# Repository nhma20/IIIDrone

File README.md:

# IIIDrone
Hardware and software specifications for the Infrastructure Inspection and Interaction Drone

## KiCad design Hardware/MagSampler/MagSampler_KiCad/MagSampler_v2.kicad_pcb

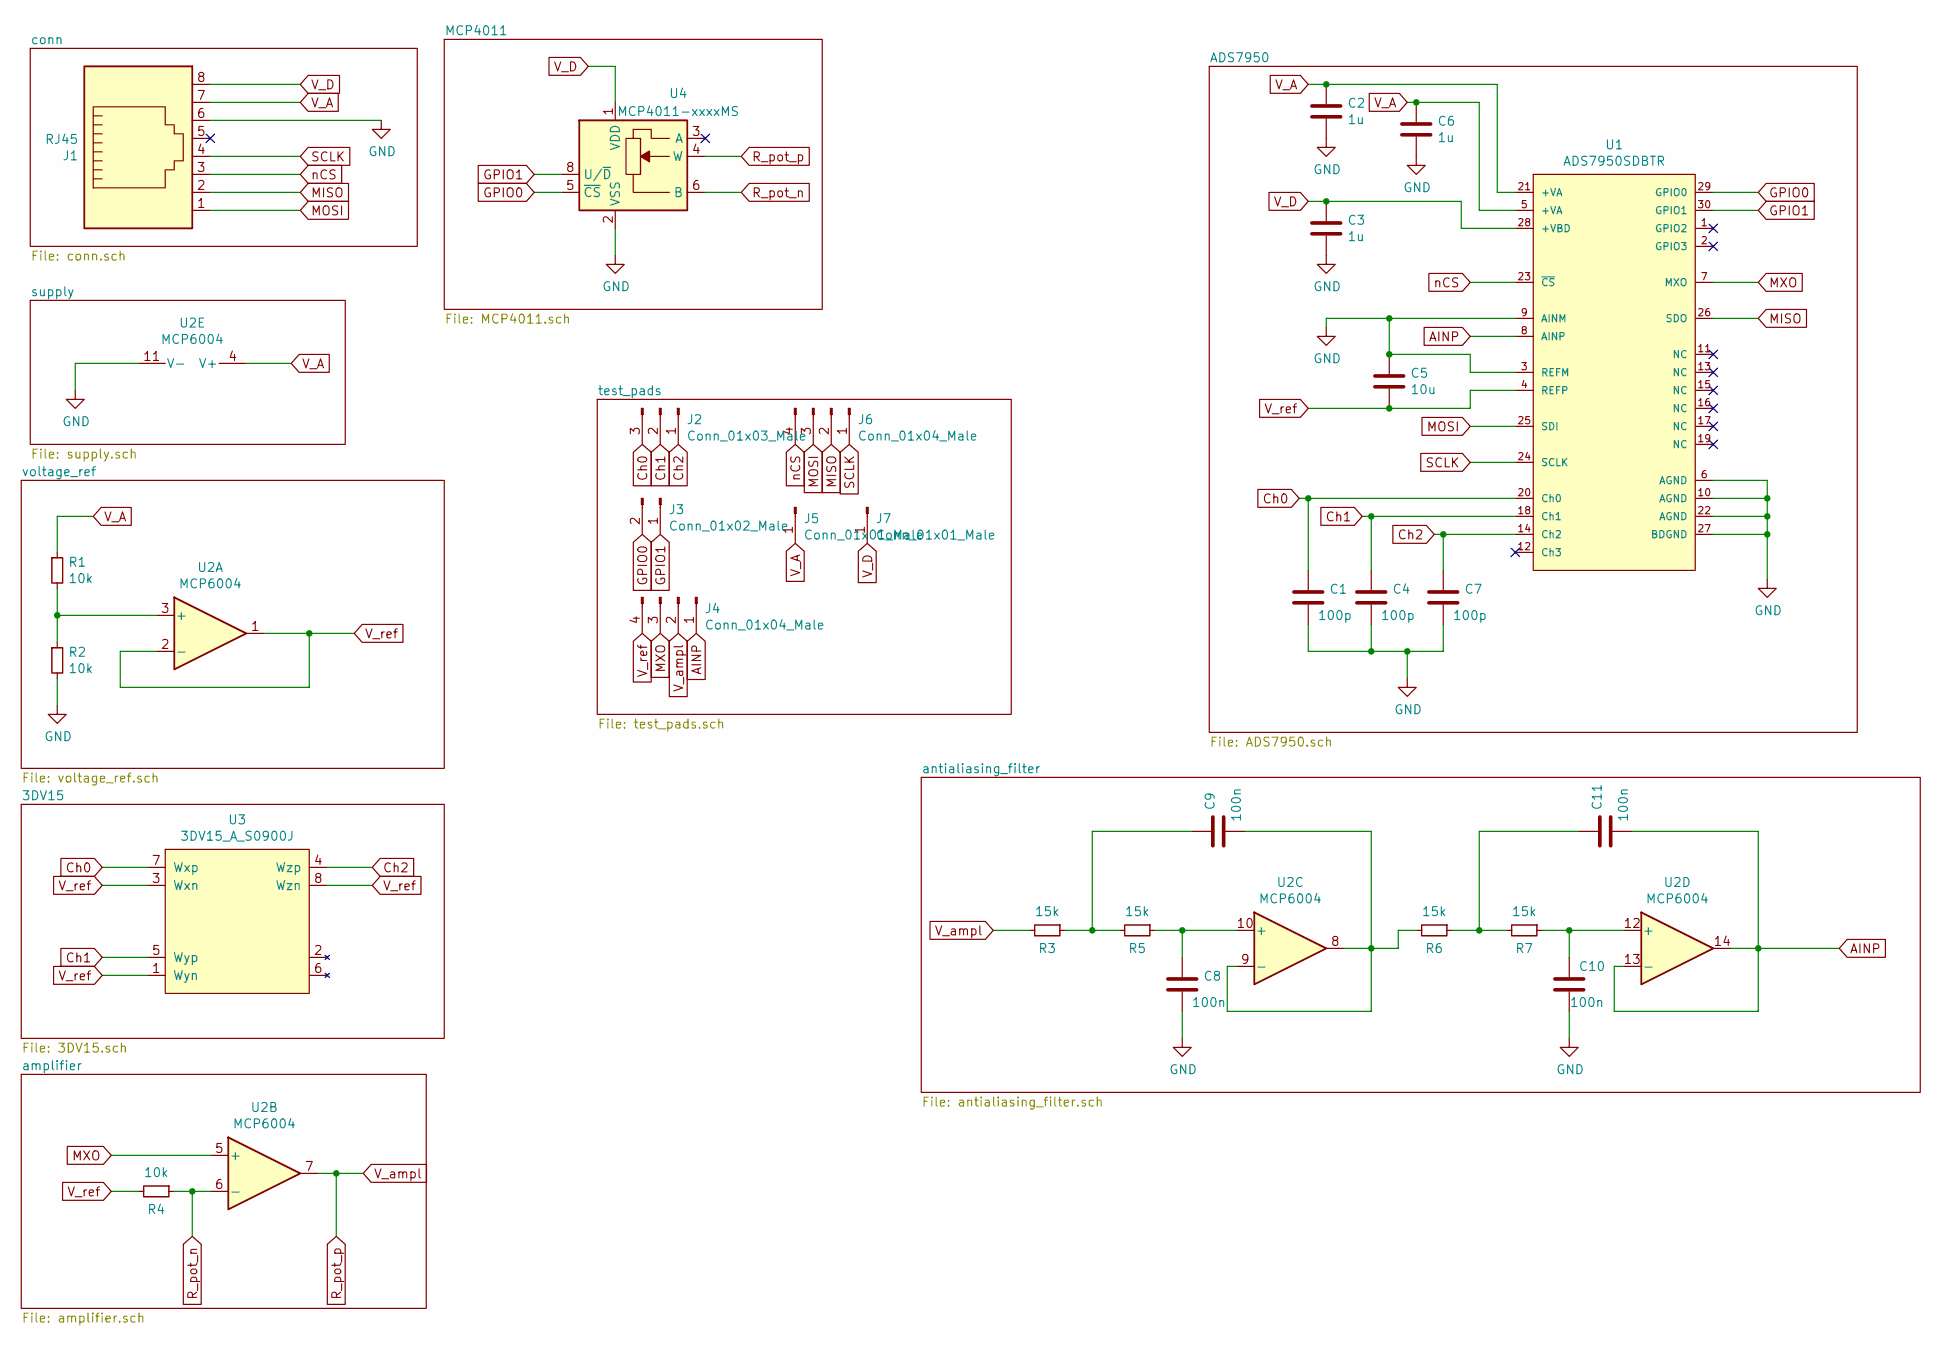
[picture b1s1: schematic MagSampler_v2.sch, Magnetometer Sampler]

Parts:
C1, C4, C7: 100p; C_0805_2012Metric
C2, C3, C6: 1u; C_0805_2012Metric
C5: 10u; C_0805_2012Metric
C8, C9, C10, C11: 100n; C_0805_2012Metric
J1: RJ45; RJ45_Ninigi_GE
J2: Conn_01x03_Male; PinHeader_1x03_P2.54mm_Vertical
J3: Conn_01x02_Male; PinHeader_1x02_P2.54mm_Vertical
J4, J6: Conn_01x04_Male; PinHeader_1x04_P2.54mm_Vertical
J5, J7: Conn_01x01_Male; PinHeader_1x01_P2.54mm_Vertical
R1, R2, R4: 10k; R_0805_2012Metric
R3, R5, R6, R7: 15k; R_0805_2012Metric
U1: ADS7950SDBTR; TSSOP-30_4.4x7.8mm_P0.5mm; mouser part number 595-ADS7950SDBTR; digikey description IC ADC 12BIT SER 1M 30TSSOP
U2: MCP6004; TSSOP-14_4.4x5mm_P0.65mm
U3: 3DV15_A_S0900J
U4: MCP4011-xxxxMS; MSOP-8_3x3mm_P0.65mm

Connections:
AINP: C11.2, J4.1, U1.8 (AINP), U2.13 (-), U2.14
Ch0: C1.1, J2.3, U1.20 (Ch0), U3.7 (Wxp)
Ch1: C4.1, J2.2, U1.18 (Ch1), U3.5 (Wyp)
Ch2: C7.1, J2.1, U1.14 (Ch2), U3.4 (Wzp)
GND: C1.2, C2.2, C3.2, C4.2, C5.1, C6.2, C7.2, C8.2, C10.2, J1.6, R2.2, U1.3 (REFM), U1.6 (AGND), U1.9 (AINM), U1.10 (AGND), U1.22 (AGND), U1.27 (BDGND), U2.11 (V-), U4.2 (VSS)
GPIO0: J3.2, U1.29 (GPIO0), U4.5 (~CS)
GPIO1: J3.1, U1.30 (GPIO1), U4.8 (U/~D)
MISO: J1.2, J6.2, U1.26 (SDO)
MOSI: J1.1, J6.3, U1.25 (SDI)
MXO: J4.3, U1.7 (MXO), U2.5 (+)
unnamed: C8.1, R5.1, U2.10 (+)
unnamed: C9.1, R3.1, R5.2
unnamed: C9.2, R6.2, U2.8, U2.9 (-)
unnamed: C10.1, R7.1, U2.12 (+)
unnamed: C11.1, R6.1, R7.2
unnamed: R1.2, R2.1, U2.3 (+)
R_pot_n: R4.1, U2.6 (-), U4.6 (B)
R_pot_p: J4.2, R3.2, U2.7, U4.4 (W)
SCLK: J1.4, J6.1, U1.24 (SCLK)
V_A: C2.1, C6.1, J1.7, J5.1, R1.1, U1.5 (+VA), U1.21 (+VA), U2.4 (V+)
V_D: C3.1, J1.8, J7.1, U1.28 (+VBD), U4.1 (VDD)
V_ref: C5.2, J4.4, R4.2, U1.4 (REFP), U2.1, U2.2 (-), U3.1 (Wyn), U3.3 (Wxn), U3.8 (Wzn)
nCS: J1.3, J6.4, U1.23 (~CS~)

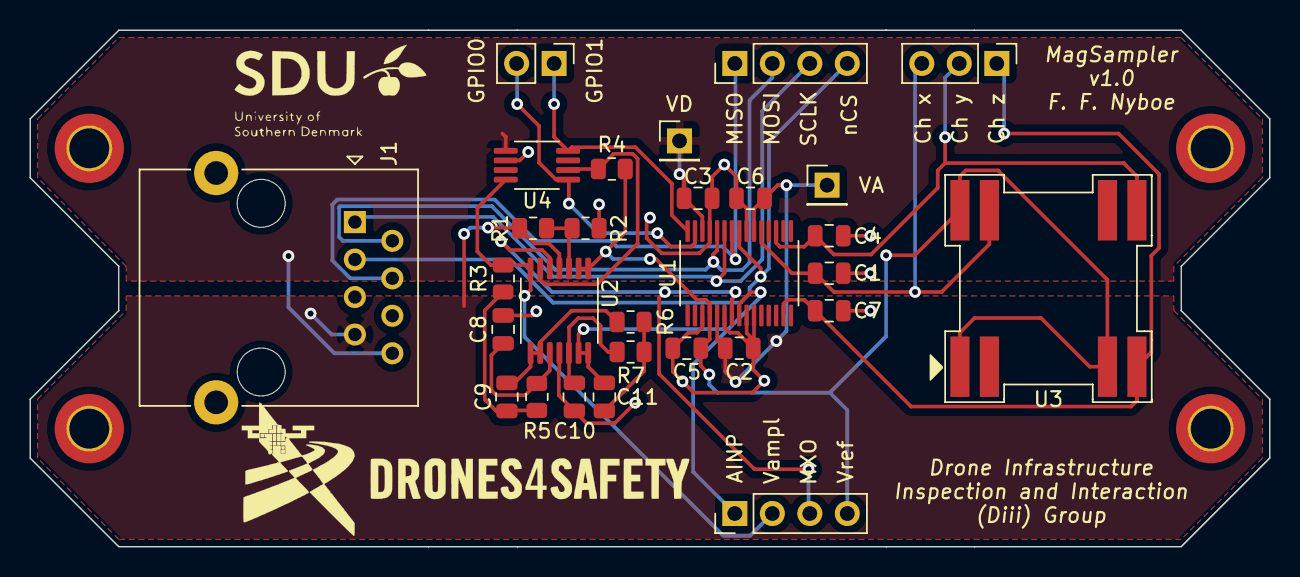
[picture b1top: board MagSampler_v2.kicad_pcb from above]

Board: 2 copper layers, 84.0 x 35.0 mm, 29 parts (0 on the bottom side), 23 nets.

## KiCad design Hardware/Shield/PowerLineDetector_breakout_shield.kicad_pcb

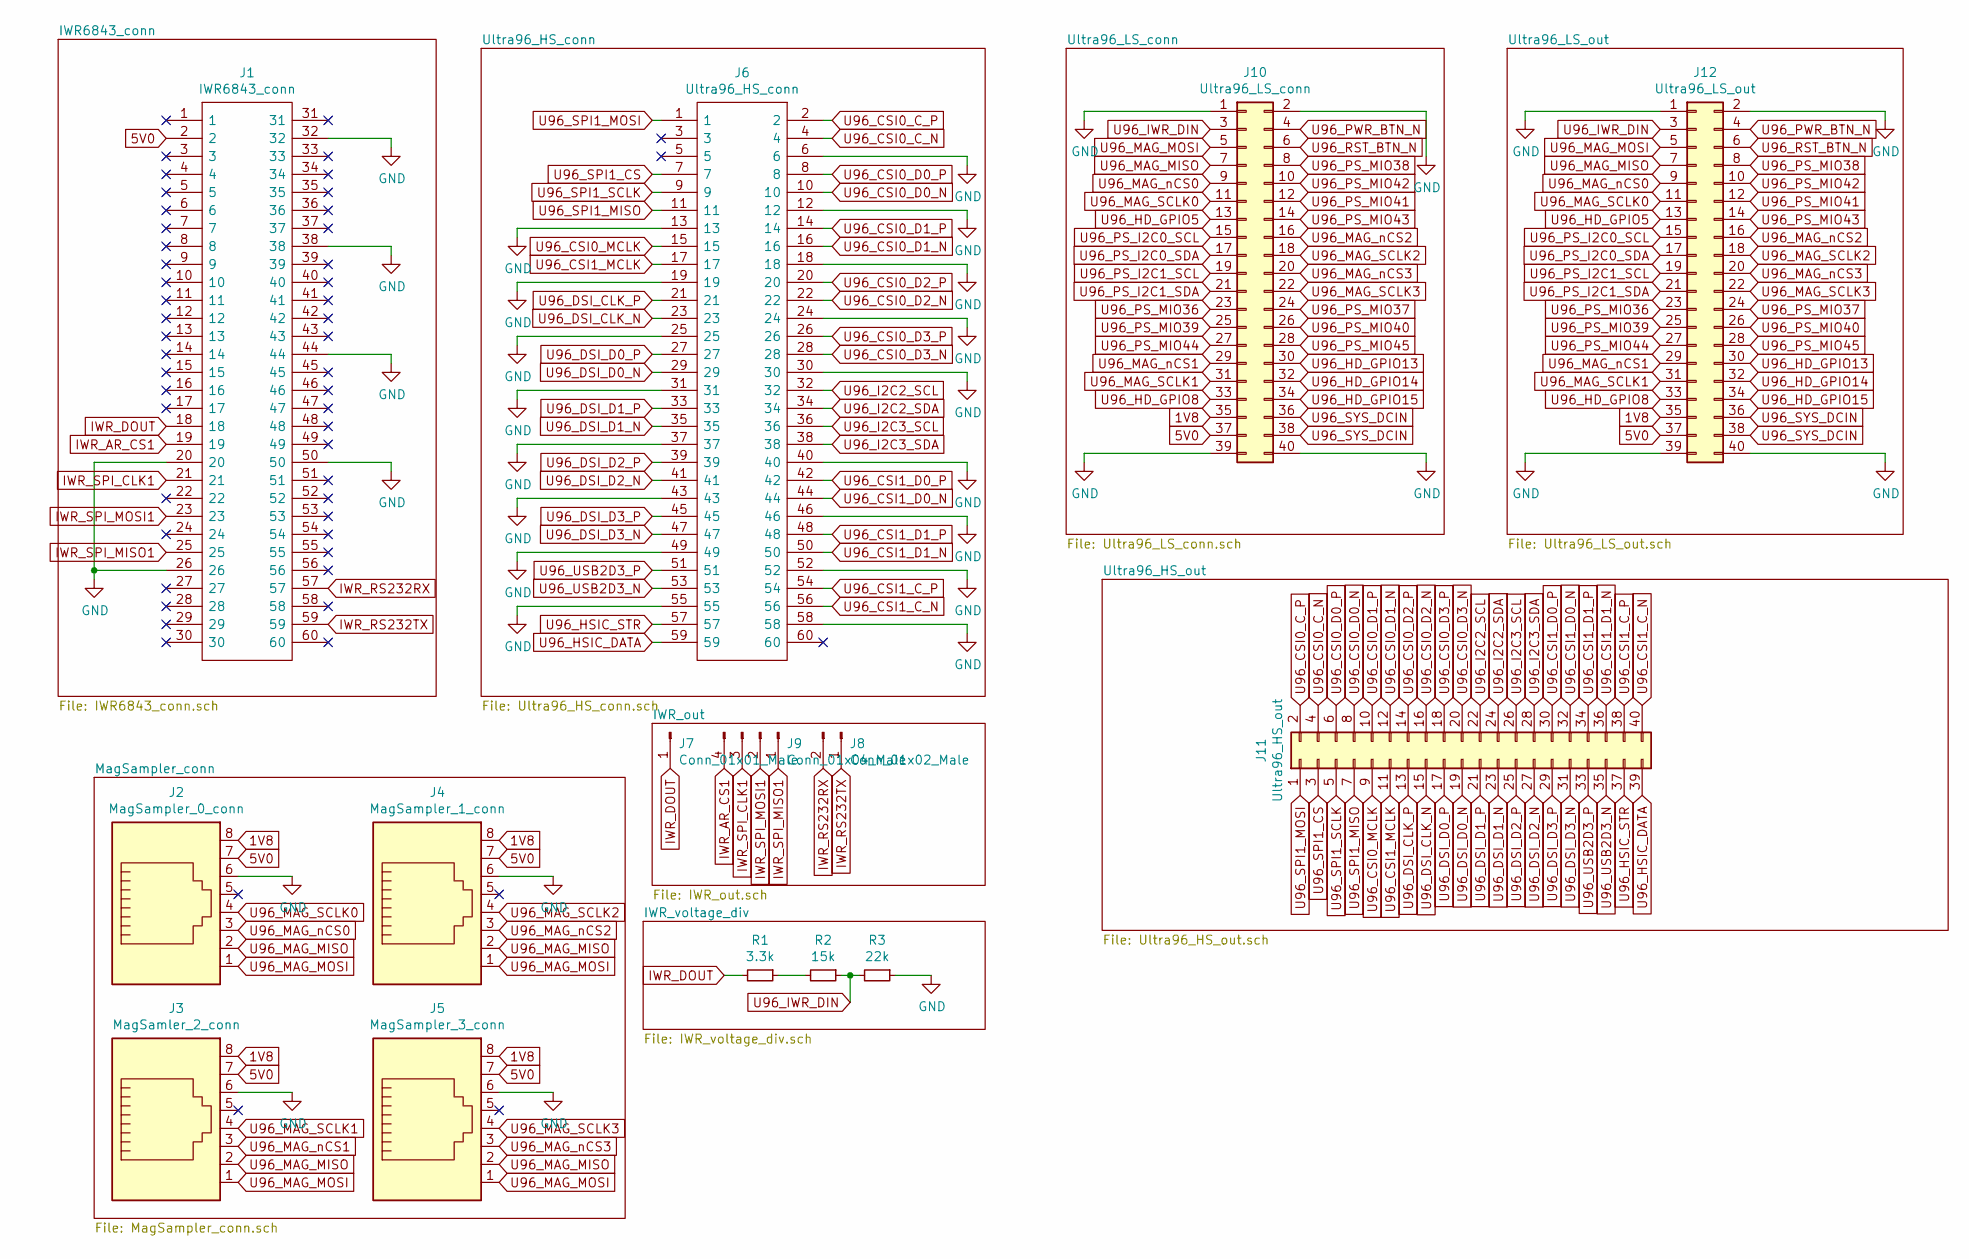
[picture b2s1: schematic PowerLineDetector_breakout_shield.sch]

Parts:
J1: IWR6843_conn; QTH-030-XX-Y-D-A-K-TR; Mouser Part Number 200-QTH03001LDAKTR
J2: MagSampler_0_conn; RJ45_Ninigi_GE
J3: MagSamler_2_conn; RJ45_Ninigi_GE
J4: MagSampler_1_conn; RJ45_Ninigi_GE
J5: MagSampler_3_conn; RJ45_Ninigi_GE
J6: Ultra96_HS_conn; 61083061402LF; Mouser Part Number 649-61083-061402LF
J7: Conn_01x01_Male; PinHeader_1x01_P2.54mm_Vertical
J8: Conn_01x02_Male; PinHeader_1x02_P2.54mm_Vertical
J9: Conn_01x04_Male; PinHeader_1x04_P2.54mm_Vertical
J10: Ultra96_LS_conn; PinSocket_2x20_P2.00mm_Vertical
J11: Ultra96_HS_out; PinHeader_2x20_P2.00mm_Vertical
J12: Ultra96_LS_out; PinHeader_2x20_P2.00mm_Vertical
R1: 3.3k; R_0805_2012Metric
R2: 15k; R_0805_2012Metric
R3: 22k; R_0805_2012Metric

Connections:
1V8: J2.8, J3.8, J4.8, J5.8, J10.35, J12.35
5V0: J1.2, J2.7, J3.7, J4.7, J5.7, J10.37, J12.37
GND: J1.20, J1.26, J1.32, J1.38, J1.44, J1.50, J2.6, J3.6, J4.6, J5.6, J6.6, J6.12, J6.13, J6.18, J6.19, J6.24, J6.25, J6.30, J6.31, J6.37, J6.40, J6.43, J6.46, J6.49, J6.52, J6.55, J6.58, J10.1, J10.2, J10.39, J10.40, J12.1, J12.2, J12.39, J12.40, R3.1
IWR_AR_CS1: J1.19, J9.4
IWR_DOUT: J1.18, J7.1, R1.2
IWR_RS232RX: J1.57, J8.2
IWR_RS232TX: J1.59, J8.1
IWR_SPI_CLK1: J1.21, J9.3
IWR_SPI_MISO1: J1.25, J9.1
IWR_SPI_MOSI1: J1.23, J9.2
unnamed: R1.1, R2.2
U96_CSI0_C_N: J6.4, J11.4
U96_CSI0_C_P: J6.2, J11.2
U96_CSI0_D0_N: J6.10, J11.8
U96_CSI0_D0_P: J6.8, J11.6
U96_CSI0_D1_N: J6.16, J11.12
U96_CSI0_D1_P: J6.14, J11.10
U96_CSI0_D2_N: J6.22, J11.16
U96_CSI0_D2_P: J6.20, J11.14
U96_CSI0_D3_N: J6.28, J11.20
U96_CSI0_D3_P: J6.26, J11.18
U96_CSI0_MCLK: J6.15, J11.9
U96_CSI1_C_N: J6.56, J11.40
U96_CSI1_C_P: J6.54, J11.38
U96_CSI1_D0_N: J6.44, J11.32
U96_CSI1_D0_P: J6.42, J11.30
U96_CSI1_D1_N: J6.50, J11.36
U96_CSI1_D1_P: J6.48, J11.34
U96_CSI1_MCLK: J6.17, J11.11
U96_DSI_CLK_N: J6.23, J11.15
U96_DSI_CLK_P: J6.21, J11.13
U96_DSI_D0_N: J6.29, J11.19
U96_DSI_D0_P: J6.27, J11.17
U96_DSI_D1_N: J6.35, J11.23
U96_DSI_D1_P: J6.33, J11.21
U96_DSI_D2_N: J6.41, J11.27
U96_DSI_D2_P: J6.39, J11.25
U96_DSI_D3_N: J6.47, J11.31
U96_DSI_D3_P: J6.45, J11.29
U96_HD_GPIO5: J10.13, J12.13
U96_HD_GPIO8: J10.33, J12.33
U96_HD_GPIO13: J10.30, J12.30
U96_HD_GPIO14: J10.32, J12.32
U96_HD_GPIO15: J10.34, J12.34
U96_HSIC_DATA: J6.59, J11.39
U96_HSIC_STR: J6.57, J11.37
U96_I2C2_SCL: J6.32, J11.22
U96_I2C2_SDA: J6.34, J11.24
U96_I2C3_SCL: J6.36, J11.26
U96_I2C3_SDA: J6.38, J11.28
U96_IWR_DIN: J10.3, J12.3, R2.1, R3.2
U96_MAG_MISO: J2.2, J3.2, J4.2, J5.2, J10.7, J12.7
U96_MAG_MOSI: J2.1, J3.1, J4.1, J5.1, J10.5, J12.5
U96_MAG_SCLK0: J2.4, J10.11, J12.11
U96_MAG_SCLK1: J3.4, J10.31, J12.31
U96_MAG_SCLK2: J4.4, J10.18, J12.18
U96_MAG_SCLK3: J5.4, J10.22, J12.22
U96_MAG_nCS0: J2.3, J10.9, J12.9
U96_MAG_nCS1: J3.3, J10.29, J12.29
U96_MAG_nCS2: J4.3, J10.16, J12.16
U96_MAG_nCS3: J5.3, J10.20, J12.20
U96_PS_I2C0_SCL: J10.15, J12.15
U96_PS_I2C0_SDA: J10.17, J12.17
U96_PS_I2C1_SCL: J10.19, J12.19
U96_PS_I2C1_SDA: J10.21, J12.21
U96_PS_MIO36: J10.23, J12.23
U96_PS_MIO37: J10.24, J12.24
U96_PS_MIO38: J10.8, J12.8
U96_PS_MIO39: J10.25, J12.25
U96_PS_MIO40: J10.26, J12.26
U96_PS_MIO41: J10.12, J12.12
U96_PS_MIO42: J10.10, J12.10
U96_PS_MIO43: J10.14, J12.14
U96_PS_MIO44: J10.27, J12.27
U96_PS_MIO45: J10.28, J12.28
U96_PWR_BTN_N: J10.4, J12.4
U96_RST_BTN_N: J10.6, J12.6
U96_SPI1_CS: J6.7, J11.3
U96_SPI1_MISO: J6.11, J11.7
U96_SPI1_MOSI: J6.1, J11.1
U96_SPI1_SCLK: J6.9, J11.5
U96_SYS_DCIN: J10.36, J10.38, J12.36, J12.38
U96_USB2D3_N: J6.53, J11.35
U96_USB2D3_P: J6.51, J11.33

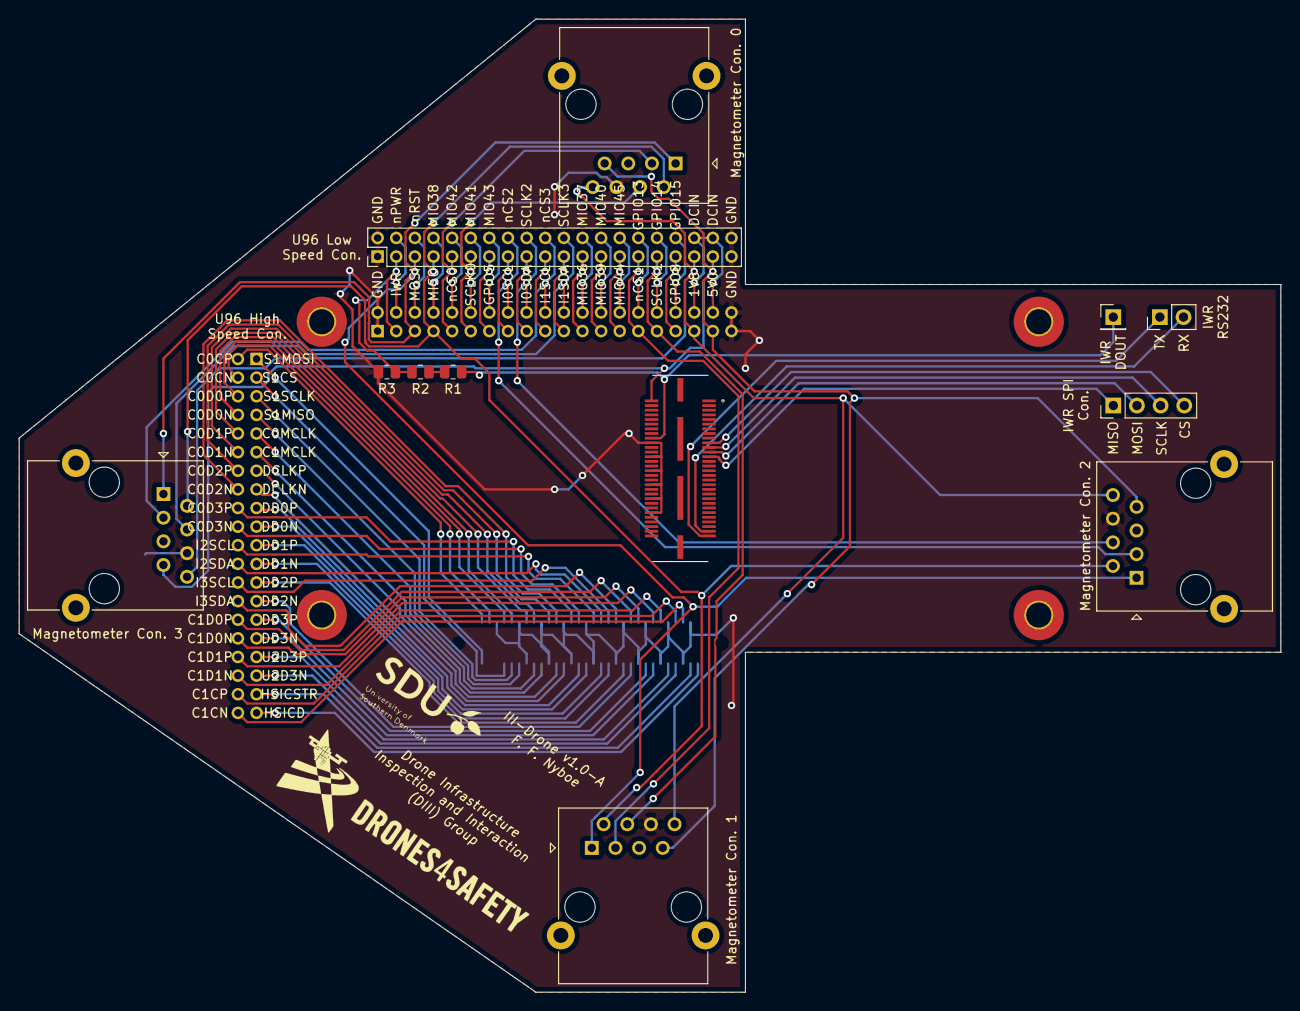
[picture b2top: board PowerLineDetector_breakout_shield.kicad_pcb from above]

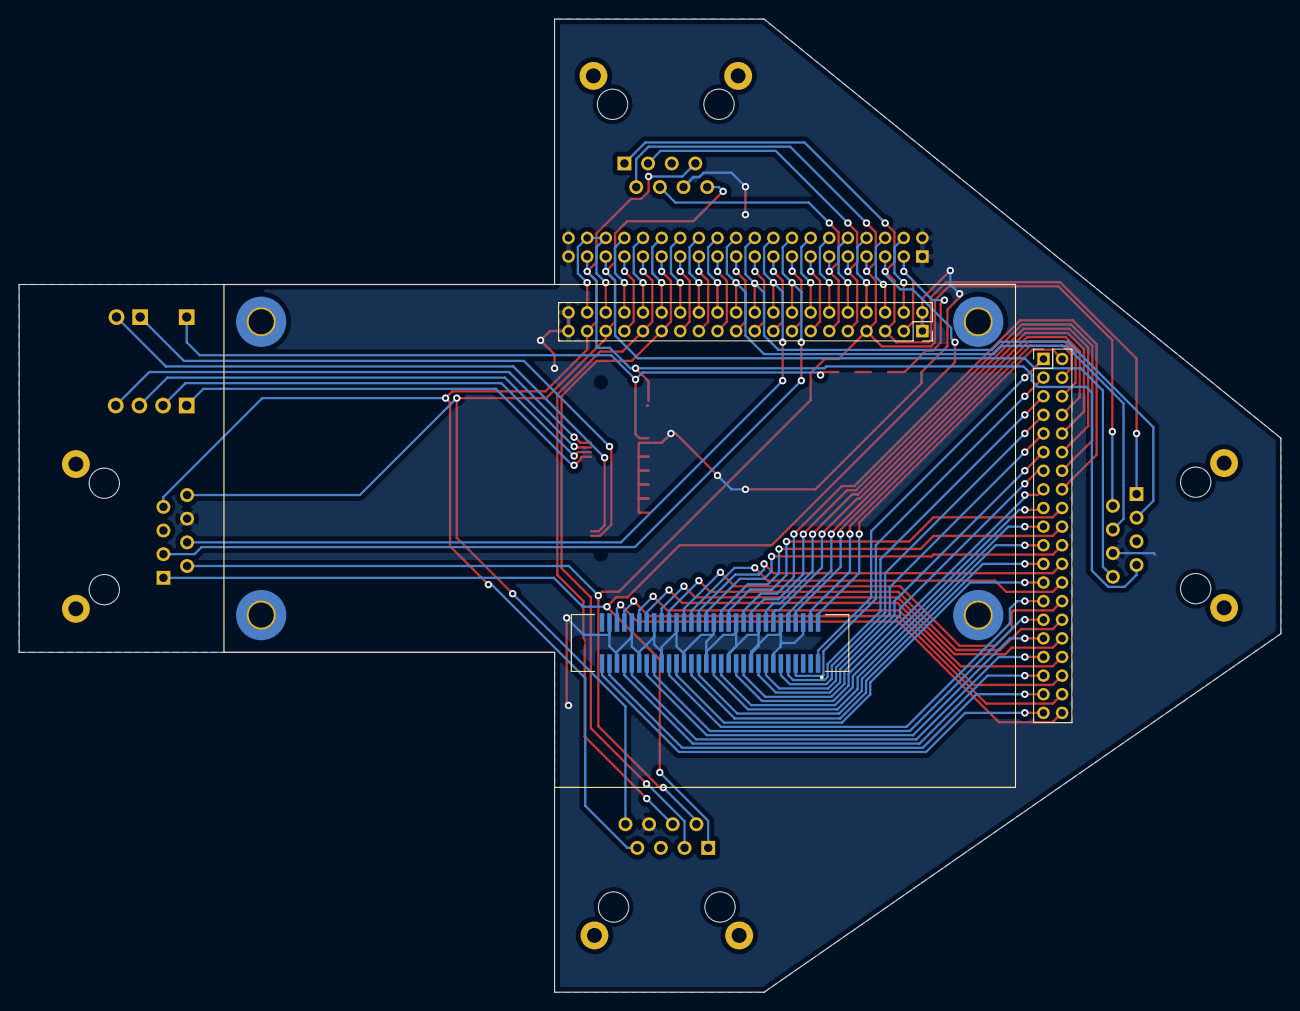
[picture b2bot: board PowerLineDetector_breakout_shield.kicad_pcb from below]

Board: 2 copper layers, 135.5 x 104.5 mm, 15 parts (3 on the bottom side), 84 nets.

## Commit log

2021-09-06 added pictures folder
2021-09-06 fixed overlapping lines
2021-09-06 Hardware specifications added
2021-09-06 added src
2021-09-06 Cleaned up KiCad projects and added PDF descriptions
2021-09-09 simulation works as intended
2021-09-09 o_address fix
2021-09-09 Added ports for mag channels
2021-09-09 include magnetometers
2021-09-09 fix bug
2021-09-09 fixed another bug
2021-09-10 clears rams before assigning
2021-09-12 added sine reconstruction
2021-09-12 o_sum_rdy
2021-09-12 fixed bug
2021-09-14 points RAM
2021-09-14 Visualization
2021-09-16 Data acquisition system files added
2021-09-17 Fixed bug in acquisition system
2021-09-21 Added vitis projects for sampling
2021-09-23 uploaded high sampling rate tests
